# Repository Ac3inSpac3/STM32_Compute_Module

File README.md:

# Custom STM32 Compute Module

## Introduction

In order to wrap my head around using KiCAD I decided to design an STM32 compute module. The goal of this exercise was to familiarise myself with the program enough so that I was comfortable designing PCBs and getting them manufactured for Uni and personal projects. Due to the high cost of manufacturing this board and the possibility of it not working it was never manufactured/tested and was purely a way for me to learn how to use KiCAD.

## Features

- STM32F4 Microcontroller
- Full breakout of GPIO pins
- Voltage Regulator with fuse
- USBC
- SWD tag connector

## Module Overview

In theory this board is capable of being the heart of many different projects as a replacement for the slow Arduino boards.

## Images

### PCB

### Schematic

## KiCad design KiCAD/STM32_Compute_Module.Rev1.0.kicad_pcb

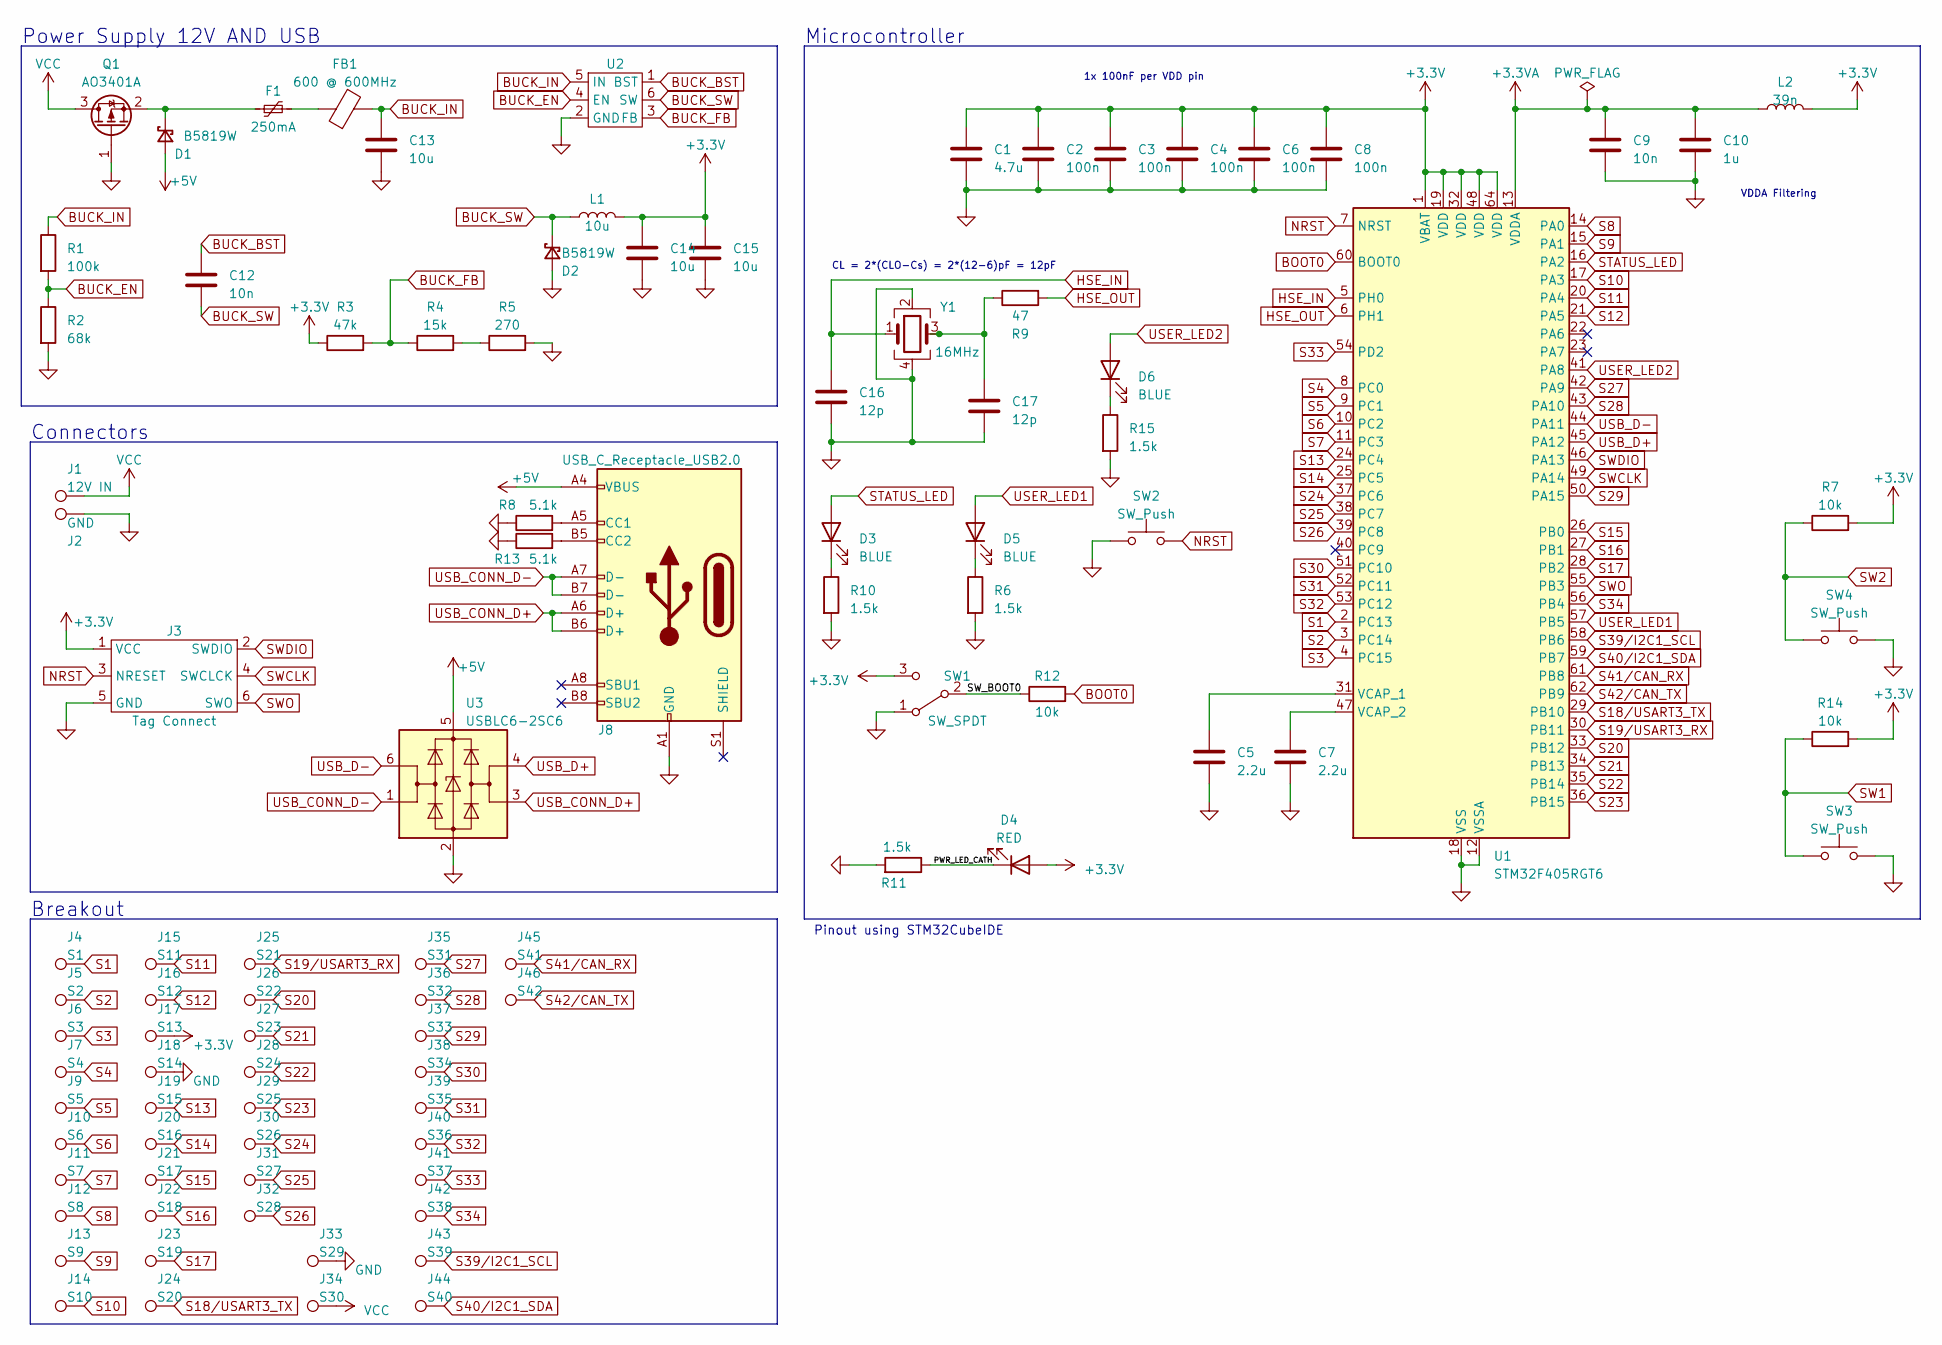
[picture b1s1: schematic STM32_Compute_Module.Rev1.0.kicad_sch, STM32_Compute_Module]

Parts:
C1: 4.7u; C_0603_1608Metric
C2, C3, C4, C6, C8: 100n; C_0402_1005Metric
C5, C7: 2.2u; C_0603_1608Metric
C9: 10n; C_0402_1005Metric
C10: 1u; C_0402_1005Metric
C12: 10n; C_0603_1608Metric
C13, C14, C15: 10u; C_1206_3216Metric
C16, C17: 12p; C_0402_1005Metric
D1, D2: B5819W; D_SOD-123
D3, D5, D6: BLUE; LED_0603_1608Metric
D4: RED; LED_0603_1608Metric
F1: 250mA; Fuse_1206_3216Metric
FB1: 600 @ 600MHz; L_0805_2012Metric
J1: 12V IN; TestPoint_Pad_2.5x2.5mm
J2: GND; TestPoint_Pad_2.5x2.5mm
J3: Tag Connect
J4: S1; Cas Pad
J5: S2; Cas Pad
J6: S3; Cas Pad
J7: S4; Cas Pad
J8: USB_C_Receptacle_USB2.0; USB_C_Receptacle_G-Switch_GT-USB-7010ASV
J9: S5; Cas Pad
J10: S6; Cas Pad
J11: S7; Cas Pad
J12: S8; Cas Pad
J13: S9; Cas Pad
J14: S10; Cas Pad
J15: S11; Cas Pad
J16: S12; Cas Pad
J17: S13; Cas Pad
J18: S14; Cas Pad
J19: S15; Cas Pad
J20: S16; Cas Pad
J21: S17; Cas Pad
J22: S18; Cas Pad
J23: S19; Cas Pad
J24: S20; Cas Pad
J25: S21; Cas Pad
J26: S22; Cas Pad
J27: S23; Cas Pad
J28: S24; Cas Pad
J29: S25; Cas Pad
J30: S26; Cas Pad
J31: S27; Cas Pad
J32: S28; Cas Pad
J33: S29; Cas Pad
J34: S30; Cas Pad
J35: S31; Cas Pad
J36: S32; Cas Pad
J37: S33; Cas Pad
J38: S34; Cas Pad
J39: S35; Cas Pad
J40: S36; Cas Pad
J41: S37; Cas Pad
J42: S38; Cas Pad
J43: S39; Cas Pad
J44: S40; Cas Pad
J45: S41; Cas Pad
J46: S42; Cas Pad
L1: 10u; L_Sunlord_MWSA0518S
L2: 39n; L_0402_1005Metric
Q1: AO3401A; SOT-23
R1: 100k; R_0603_1608Metric
R2: 68k; R_0603_1608Metric
R3: 47k; R_0603_1608Metric
R4: 15k; R_0603_1608Metric
R5: 270; R_0603_1608Metric
R6, R10, R11, R15: 1.5k; R_0603_1608Metric
R7, R14: 10k; R_0603_1608Metric
R8, R13: 5.1k; R_0402_1005Metric
R9: 47; R_0402_1005Metric
R12: 10k; R_0402_1005Metric
SW1: SW_SPDT; SW_SPDT_PCM12
SW2, SW3, SW4: SW_Push; SW_SPST_B3U-1000P
U1: STM32F405RGT6; LQFP-64_10x10mm_P0.5mm
U2: TSOT-23-6
U3: USBLC6-2SC6; SOT-23-6
Y1: 16MHz; Crystal_SMD_3225-4Pin_3.2x2.5mm

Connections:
+3.3V: C1.1, C2.1, C3.1, C4.1, C6.1, C8.1, C14.1, C15.1, D4.2 (A), J3.1 (VCC), J17.1, L1.2, L2.2, R3.1, R7.2, R14.2, SW1.3 (C), U1.1 (VBAT), U1.19 (VDD), U1.32 (VDD), U1.48 (VDD), U1.64 (VDD)
+3.3VA: C9.1, C10.1, L2.1, U1.13 (VDDA)
+5V: D1.2 (A), J8.A4 (VBUS), J8.A9 (VBUS), J8.B4 (VBUS), J8.B9 (VBUS), U3.5 (VBUS)
/PWR_LED_CATH: D4.1 (K), R11.1
/SW_BOOT0: R12.1, SW1.2 (B)
BOOT0: R12.2, U1.60 (BOOT0)
BUCK_BST: C12.1, U2.1 (BST)
BUCK_EN: R1.2, R2.1, U2.4 (EN)
BUCK_FB: R3.2, R4.1, U2.3 (FB)
BUCK_IN: C13.1, FB1.2, R1.1, U2.5 (IN)
BUCK_SW: C12.2, D2.1 (K), L1.1, U2.6 (SW)
GND: C1.2, C2.2, C3.2, C4.2, C5.2, C6.2, C7.2, C8.2, C9.2, C10.2, C13.2, C14.2, C15.2, C16.2, C17.2, D2.2 (A), J2.1, J3.5 (GND), J8.A1 (GND), J8.A12 (GND), J8.B1 (GND), J8.B12 (GND), J18.1, J33.1, Q1.1 (G), R2.2, R5.2, R6.2, R8.1, R10.2, R11.2, R13.1, R15.2, SW1.1 (A), SW2.1, SW3.1, SW4.1, U1.12 (VSSA), U1.18 (VSS), U1.63 (VSS), U2.2 (GND), U3.2 (GND), Y1.2, Y1.4
HSE_IN: C16.1, U1.5 (PH0), Y1.1
HSE_OUT: R9.2, U1.6 (PH1)
NRST: J3.3 (NRESET), SW2.2, U1.7 (NRST)
unnamed: C17.1, R9.1, Y1.3
unnamed: D1.1 (K), F1.1, Q1.2 (S)
unnamed: D3.1 (K), R10.1
unnamed: D5.1 (K), R6.1
unnamed: D6.1 (K), R15.1
unnamed: F1.2, FB1.1
unnamed: J8.A5 (CC1), R8.2
unnamed: J8.B5 (CC2), R13.2
unnamed: R4.2, R5.1
unnamed: C5.1, U1.31 (VCAP_1)
unnamed: C7.1, U1.47 (VCAP_2)
S1: J4.1, U1.2 (PC13)
S2: J5.1, U1.3 (PC14)
S3: J6.1, U1.4 (PC15)
S4: J7.1, U1.8 (PC0)
S5: J9.1, U1.9 (PC1)
S6: J10.1, U1.10 (PC2)
S7: J11.1, U1.11 (PC3)
S8: J12.1, U1.14 (PA0)
S9: J13.1, U1.15 (PA1)
S10: J14.1, U1.17 (PA3)
S11: J15.1, U1.20 (PA4)
S12: J16.1, U1.21 (PA5)
S13: J19.1, U1.24 (PC4)
S14: J20.1, U1.25 (PC5)
S15: J21.1, U1.26 (PB0)
S16: J22.1, U1.27 (PB1)
S17: J23.1, U1.28 (PB2)
S18/USART3_TX: J24.1, U1.29 (PB10)
S19/USART3_RX: J25.1, U1.30 (PB11)
S20: J26.1, U1.33 (PB12)
S21: J27.1, U1.34 (PB13)
S22: J28.1, U1.35 (PB14)
S23: J29.1, U1.36 (PB15)
S24: J30.1, U1.37 (PC6)
S25: J31.1, U1.38 (PC7)
S26: J32.1, U1.39 (PC8)
S27: J35.1, U1.42 (PA9)
S28: J36.1, U1.43 (PA10)
S29: J37.1, U1.50 (PA15)
S30: J38.1, U1.51 (PC10)
S31: J39.1, U1.52 (PC11)
S32: J40.1, U1.53 (PC12)
S33: J41.1, U1.54 (PD2)
S34: J42.1, U1.56 (PB4)
S39/I2C1_SCL: J43.1, U1.58 (PB6)
S40/I2C1_SDA: J44.1, U1.59 (PB7)
S41/CAN_RX: J45.1, U1.61 (PB8)
S42/CAN_TX: J46.1, U1.62 (PB9)
STATUS_LED: D3.2 (A), U1.16 (PA2)
SW1: R14.1, SW3.2
SW2: R7.1, SW4.2
SWCLK: J3.4 (SWCLCK), U1.49 (PA14)
SWDIO: J3.2 (SWDIO), U1.46 (PA13)
SWO: J3.6 (SWO), U1.55 (PB3)
USB_CONN_D+: J8.A6 (D+), J8.B6 (D+), U3.3 (I/O2)
USB_CONN_D-: J8.A7 (D-), J8.B7 (D-), U3.1 (I/O1)
USB_D+: U1.45 (PA12), U3.4 (I/O2)
USB_D-: U1.44 (PA11), U3.6 (I/O1)
USER_LED1: D5.2 (A), U1.57 (PB5)
USER_LED2: D6.2 (A), U1.41 (PA8)
VCC: J1.1, J34.1, Q1.3 (D)

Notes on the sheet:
1x 100nF per VDD pin
Power Supply 12V AND USB
CL = 2*(CLO-Cs) = 2*(12-6)pF = 12pF
Breakout
VDDA Filtering
Microcontroller
Connectors
Pinout using STM32CubeIDE

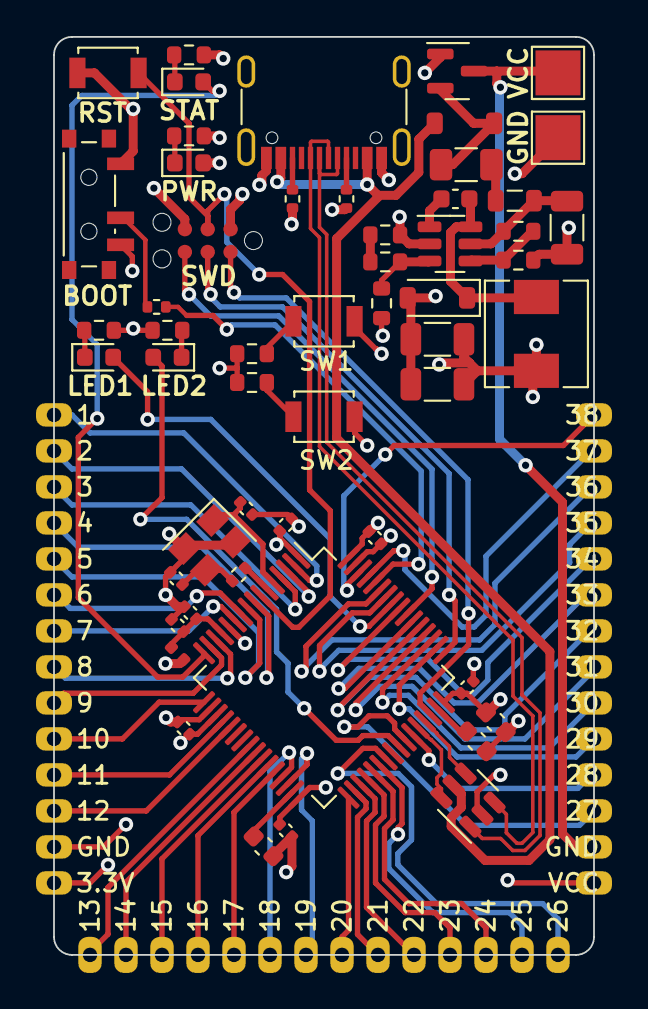
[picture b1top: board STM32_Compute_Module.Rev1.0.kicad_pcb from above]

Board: 4 copper layers, 30.0 x 51.0 mm, 96 parts (0 on the bottom side), 77 nets.

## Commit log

2023-06-13 Added PCB KiCAD
2023-06-14 Folder Name Update
2023-06-14 Added manufacturing files and renamed
2023-06-14 Added JLC PCB serial number location
